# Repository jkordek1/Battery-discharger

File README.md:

# Battery discharger

## Why do you need this?

If you have a lot of 18650 Li-Ion battery cells that you won't be using any time soon you need to discharge them. In order for cells to stay healthy and remain their capacirty, they need to be stored at 50% of capacity (3.7 - 3.8V).
This device discharges the batteries to the storage level voltage.

## What is it?

 Automated battery discharger for Li-Po and Li-Ion batteries powered by ATmega328p microcontroller.
 Used for safely discharging 4 single-cell 18650 batteries to a storage level voltage (3.7V).
 No need for external power, the circuit is powered from cell #1.
 
 First push button switches between voltage and current monitoring.
 Second push button is used for manual voltage level measurement and for deactivating the buzzer.
 
 The code is written in Arduino and is available to download.
 
 The device is functional but could be improved.
 
 ## Features
 
 - 1.3" OLED screen
 - 2 push buttons used as controls
 - Buzzer for audio queues
 - ISP programming port
 - 4x 18650 battery discharging at the same time
 
 ## TO-DO
 - implement voltage level selection via push buttons 

## Images

## Project folder structure
    .
    ├── ...
    ├── 3D models               # 3D models of added components
    ├── ArduinoCode             # .ino file for Arduino
    ├── Images                  # Images of the project
    ├── KiCAD_Files             # Main folder
    │   ├── bom                 # ibom folder for assembly
    │   ├── gerber              # gerber output folder
    │   └── jlcpcb              # gerber and assembly folder - addon
    └── ...

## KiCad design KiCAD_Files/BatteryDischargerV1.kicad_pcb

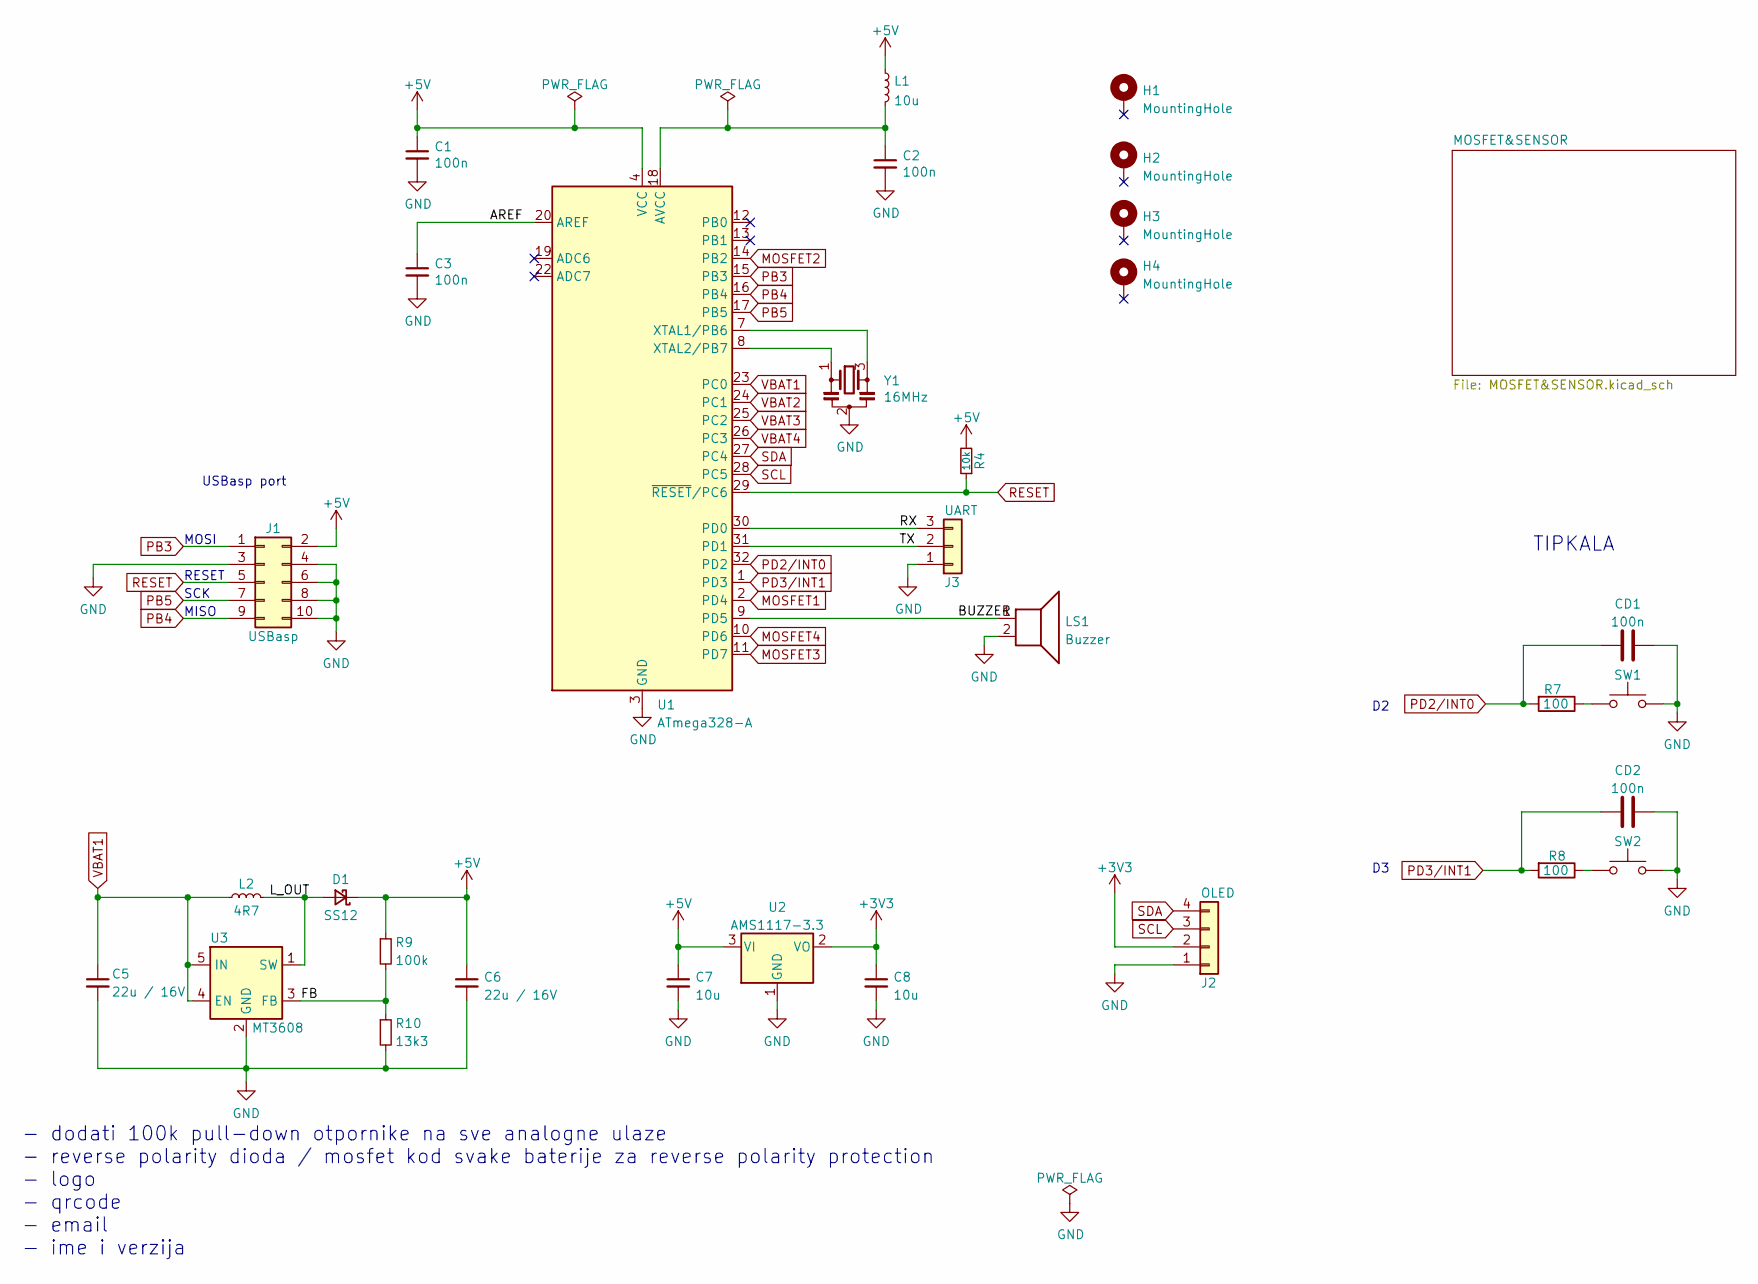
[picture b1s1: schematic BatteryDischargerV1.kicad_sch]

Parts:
C1, C2, C3: 100n; C_0603_1608Metric; JLCPCB Part # C49678
C5, C6: 22u / 16V; C_1210_3225Metric; JLCPCB Part # C337451
C7, C8: 10u; C_1210_3225Metric; JLCPCB Part # C337451
CD1, CD2: 100n; C_0603_1608Metric
D1: SS12; D_SMA; JLCPCB Part # C2985002
H1, H2, H3, H4: MountingHole; MountingHole_3.2mm_M3_Pad_Via
J1: USBasp; IDC-Header_2x05_P2.54mm_Vertical
J2: OLED
J3: UART; PinHeader_1x03_P2.54mm_Horizontal
L1: 10u; L_1206_3216Metric; JLCPCB Part # C279941
L2: 4R7; Inductor_4mm(5x5mm pads)
LS1: Buzzer; Buzzer_TDK_PS1240P02BT_D12.2mm_H6.5mm
R4: 10k; R_0603_1608Metric; JLCPCB Part # C17414
R7, R8: 100; R_0603_1608Metric
R9: 100k; R_0603_1608Metric
R10: 13k3; R_0603_1608Metric; JLCPCB Part # C185373
SW1, SW2: SW_Push; Omron_B3F-12x12mm
U1: ATmega328-A; TQFP-32_7x7mm_P0.8mm
U2: AMS1117-3.3; SOT-223-3_TabPin2
U3: MT3608; SOT-23-6; JLCPCB Part # C2932326
Y1: 16MHz; CSTCE16M0V53-R0; JLCPCB Part # C32180

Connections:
+3V3: C8.1, J2.2, U2.2 (VO)
+5V: C1.1, C6.1, C7.1, D1.1 (K), J1.2, L1.1, R4.2, R9.1, U1.4 (VCC), U1.6 (VCC), U2.3 (VI)
/AREF: C3.1, U1.20 (AREF)
/BUZZER: LS1.1, U1.9 (PD5)
/FB: R9.2, R10.1, U3.3 (FB)
/L_OUT: D1.2 (A), L2.2, U3.1 (SW)
/RX: J3.3, U1.30 (PD0)
/TX: J3.2, U1.31 (PD1)
GND: C1.2, C2.2, C3.2, C5.2, C6.2, C7.2, C8.2, CD1.2, CD2.2, J1.3, J1.4, J1.6, J1.8, J1.10, J2.1, J3.1, LS1.2, R10.2, SW1.2, SW2.2, U1.3 (GND), U1.5 (GND), U1.21 (GND), U2.1 (GND), U3.2 (GND), Y1.2; also elsewhere on the board
MOSFET1: U1.2 (PD4); also elsewhere on the board
MOSFET2: U1.14 (PB2); also elsewhere on the board
MOSFET3: U1.11 (PD7); also elsewhere on the board
MOSFET4: U1.10 (PD6); also elsewhere on the board
unnamed: C2.1, L1.2, U1.18 (AVCC)
unnamed: R7.1, SW1.1
unnamed: R8.1, SW2.1
unnamed: U1.7 (XTAL1/PB6), Y1.3
unnamed: U1.8 (XTAL2/PB7), Y1.1
PB3: J1.1, U1.15 (PB3)
PB4: J1.9, U1.16 (PB4)
PB5: J1.7, U1.17 (PB5)
PD2/INT0: CD1.1, R7.2, U1.32 (PD2)
PD3/INT1: CD2.1, R8.2, U1.1 (PD3)
RESET: J1.5, R4.1, U1.29 (~RESET/PC6)
SCL: J2.3, U1.28 (PC5)
SDA: J2.4, U1.27 (PC4)
VBAT1: C5.1, L2.1, U1.23 (PC0), U3.4 (EN), U3.5 (IN); also elsewhere on the board
VBAT2: U1.24 (PC1); also elsewhere on the board
VBAT3: U1.25 (PC2); also elsewhere on the board
VBAT4: U1.26 (PC3); also elsewhere on the board

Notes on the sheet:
USBasp port
MISO
RESET
- dodati 100k pull-down otpornike na sve analogne ulaze - reverse polarity dioda / mosfet kod svake baterije za reverse polarity protection - logo - qrcode - email - ime i verzija
SCK
TIPKALA
MOSI

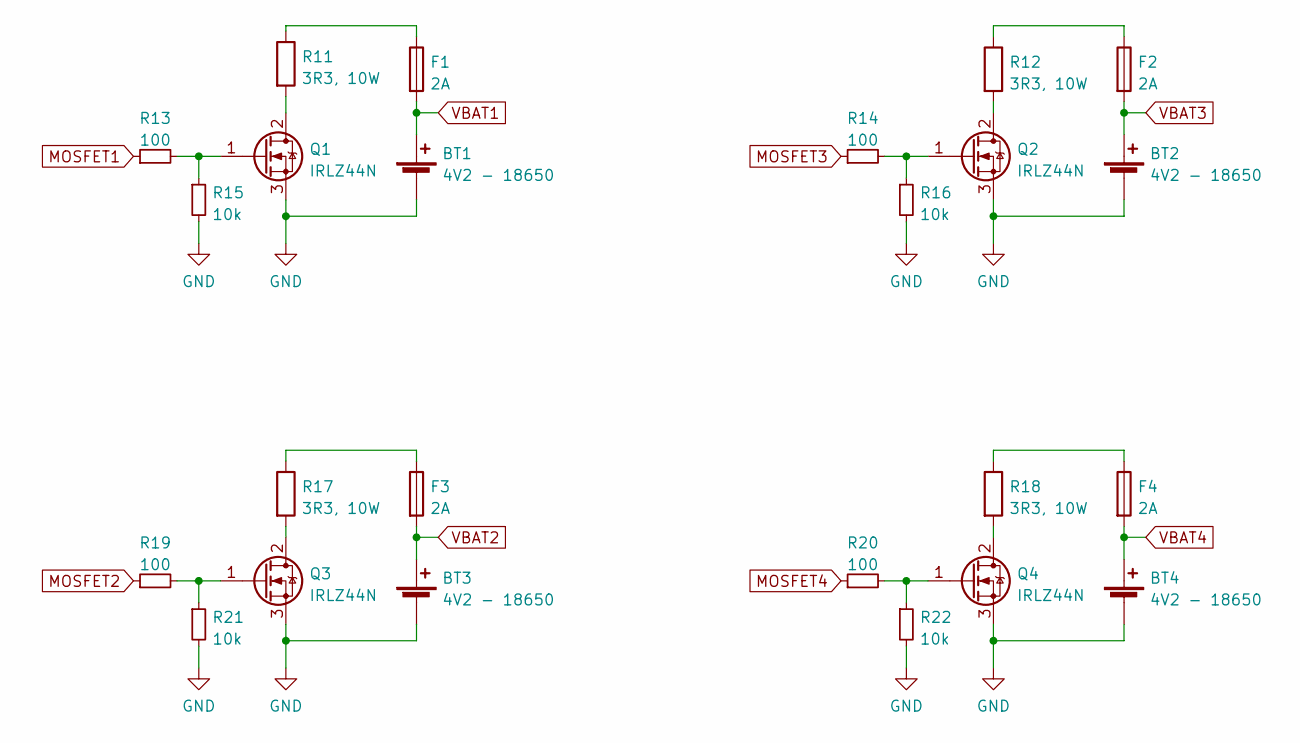
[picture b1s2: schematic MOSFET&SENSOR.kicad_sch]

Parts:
BT1, BT2, BT3, BT4: 4V2 - 18650; 18650-holder
F1, F2, F3, F4: 2A; 696108003002
Q1, Q2, Q3, Q4: IRLZ44N; TO-220-3_Horizontal_TabDown
R11, R12, R17, R18: 3R3, 10W; PRW0AWJW33JB00
R13, R14, R19, R20: 100; R_0603_1608Metric
R15, R16, R21, R22: 10k; R_0603_1608Metric

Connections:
GND: BT1.2 (-), BT2.2 (-), BT3.2 (-), BT4.2 (-), Q1.3 (S), Q2.3 (S), Q3.3 (S), Q4.3 (S), R15.2, R16.2, R21.2, R22.2; also elsewhere on the board
MOSFET1: R13.1; also elsewhere on the board
MOSFET2: R19.1; also elsewhere on the board
MOSFET3: R14.1; also elsewhere on the board
MOSFET4: R20.1; also elsewhere on the board
unnamed: F1.1, R11.1
unnamed: F2.1, R12.1
unnamed: F3.1, R17.1
unnamed: F4.1, R18.1
unnamed: Q1.1 (G), R13.2, R15.1
unnamed: Q1.2 (D), R11.2
unnamed: Q2.1 (G), R14.2, R16.1
unnamed: Q2.2 (D), R12.2
unnamed: Q3.1 (G), R19.2, R21.1
unnamed: Q3.2 (D), R17.2
unnamed: Q4.1 (G), R20.2, R22.1
unnamed: Q4.2 (D), R18.2
VBAT1: BT1.1 (+), F1.2; also elsewhere on the board
VBAT2: BT3.1 (+), F3.2; also elsewhere on the board
VBAT3: BT2.1 (+), F2.2; also elsewhere on the board
VBAT4: BT4.1 (+), F4.2; also elsewhere on the board

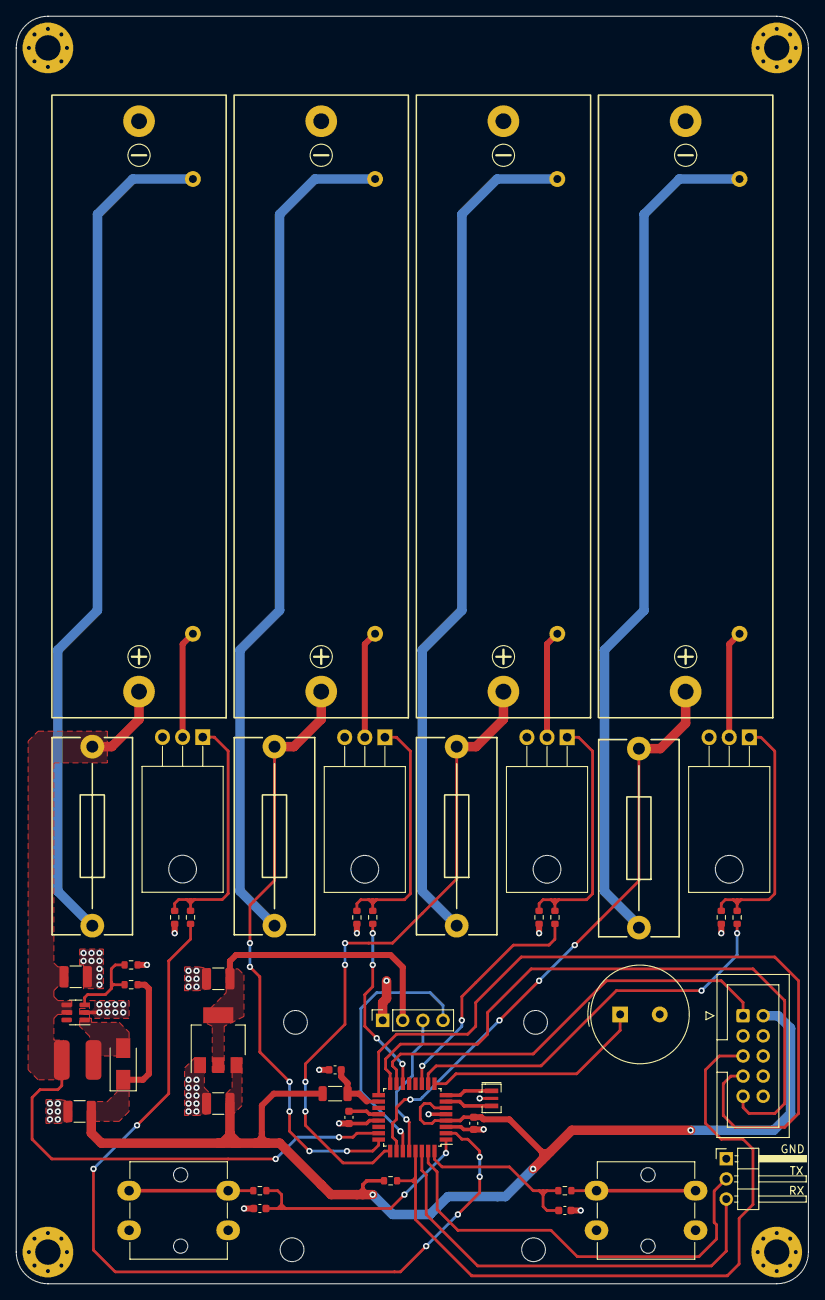
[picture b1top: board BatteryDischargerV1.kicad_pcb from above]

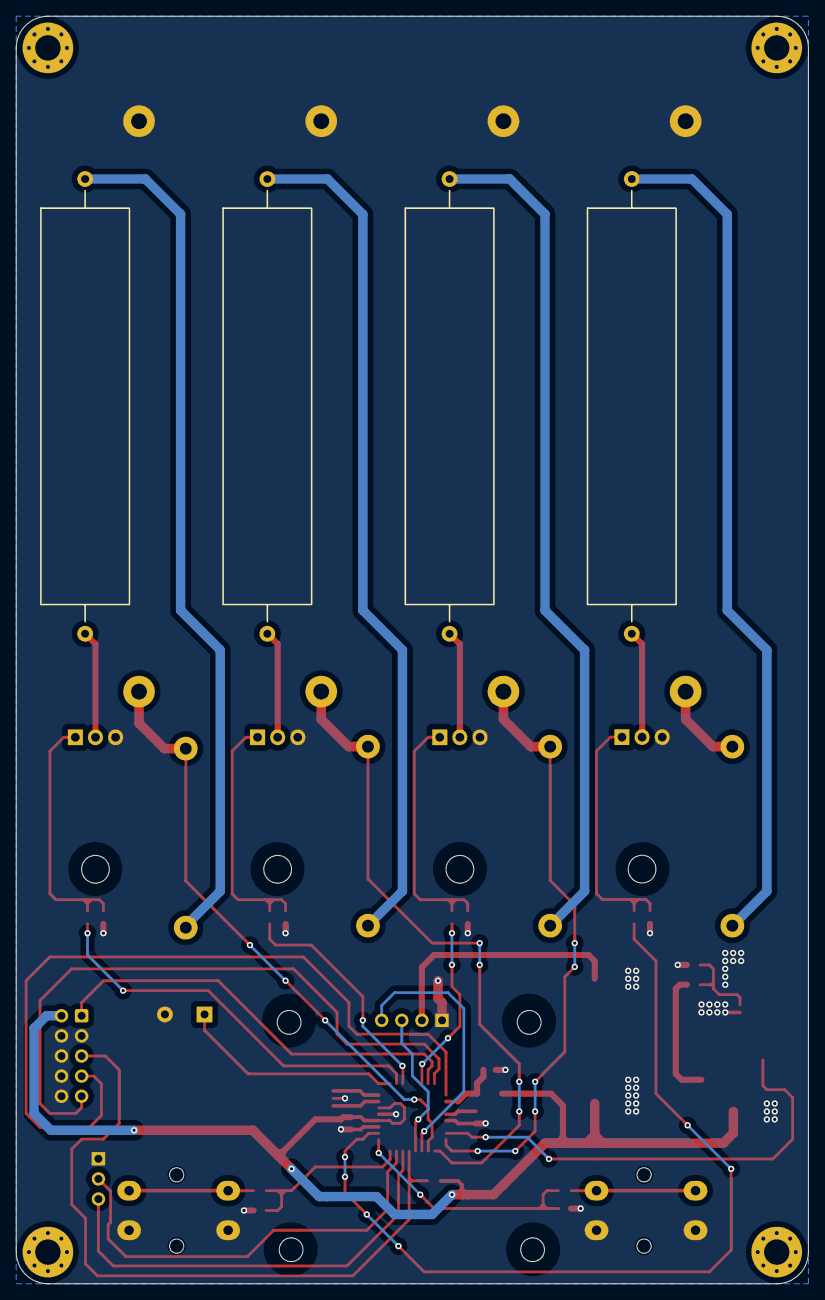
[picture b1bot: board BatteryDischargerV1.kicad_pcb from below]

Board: 2 copper layers, 100.0 x 160.0 mm, 55 parts (5 on the bottom side), 42 nets.

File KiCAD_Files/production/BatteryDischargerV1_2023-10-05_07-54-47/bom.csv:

Designator,Footprint,Quantity,Value,LCSC Part #
"BT1, BT2, BT3, BT4",18650-holder,4,4V2 - 18650,
"C1, C2, C3",0603,3,100n,C49678
"C5, C6",1210,2,22u / 16V,C337451
"C7, C8",1210,2,10u,C337451
"CD1, CD2",0603,2,100n,
D1,D_SMA,1,SS12,C2985002
"F1, F2, F3, F4",696108003002,4,2A,
"H1, H2, H3, H4",MountingHole_3.2mm_M3_Pad_Via,4,MountingHole,
J1,IDC-Header_2x05_P2.54mm_Vertical,1,USBasp,
J2,OLED,1,OLED,
J3,PinHeader_1x03_P2.54mm_Horizontal,1,UART,
L1,1206,1,10u,C279941
L2,Inductor_4mm(5x5mm pads),1,4R7,
LS1,Buzzer_TDK_PS1240P02BT_D12.2mm_H6.5mm,1,Buzzer,
"Q1, Q2, Q3, Q4",TO-220-3_Horizontal_TabDown,4,IRLZ44N,
R10,0603,1,13k3,C185373
"R11, R12, R17, R18",PRW0AWJW33JB00,4,"3R3, 10W",
"R13, R14, R19, R20, R7, R8",0603,6,100,
"R15, R16, R21, R22",0603,4,10k,
R4,0603,1,10k,C17414
R9,0603,1,100k,
"SW1, SW2",Omron_B3F-12x12mm,2,SW_Push,
U1,TQFP-32_7x7mm_P0.8mm,1,ATmega328-A,
U2,SOT-223-3_TabPin2,1,AMS1117-3.3,
U3,SOT-23-6,1,MT3608,C2932326
Y1,CSTCE16M0V53-R0,1,16MHz,C32180

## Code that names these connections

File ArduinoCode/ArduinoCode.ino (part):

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#include <Adafruit_GFX.h>
#include <Adafruit_SH110X.h>

#define buzzer 5

#define M1 4          //MOSFET1
#define M2 10         //MOSFET2
#define M3 7          //MOSFET3
#define M4 6          //MOSFET4
#define buttonPin1 3
#define buttonPin2 2

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
  Serial.begin(9600);

  pinMode(buzzer, OUTPUT);
  pinMode(M1, OUTPUT);
  pinMode(M2, OUTPUT);
  pinMode(M3, OUTPUT);
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
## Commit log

2022-12-15 Initial release
2023-02-14 kicad7
